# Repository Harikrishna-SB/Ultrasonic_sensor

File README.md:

# Ultrasonic_sensor

Interfacing ultrasonic sensor without a micro-controller

HCSR04 has 4 pins..the usual vcc,gnd and trig(stands for trigger) and echo
for more details:

This project aims to read the sensor data convert it to proper units and display on a seven segment display..

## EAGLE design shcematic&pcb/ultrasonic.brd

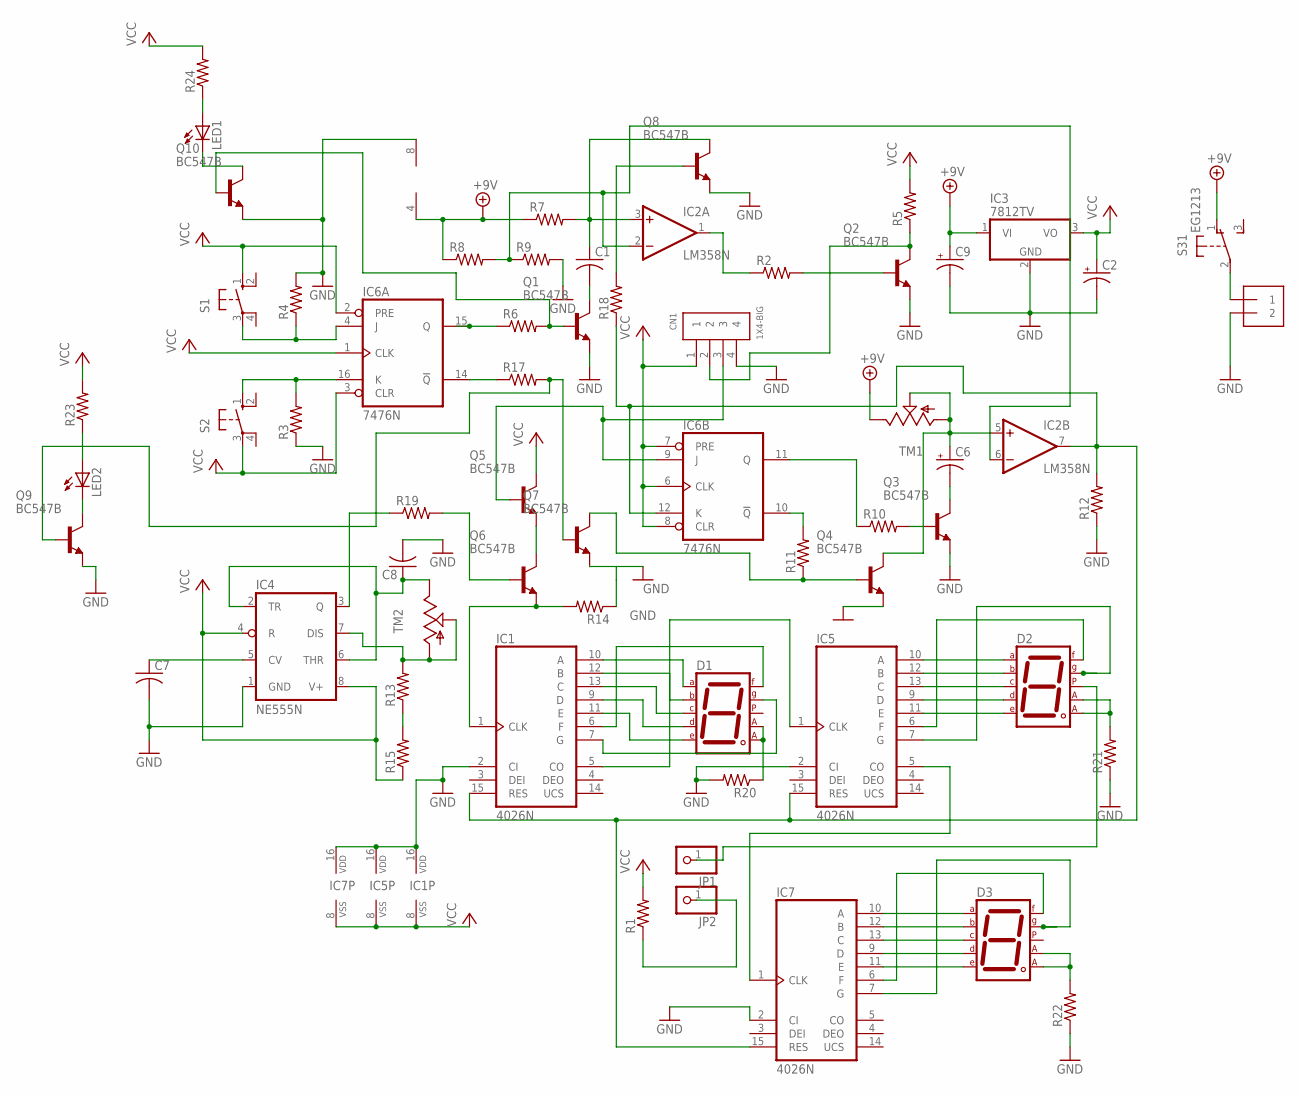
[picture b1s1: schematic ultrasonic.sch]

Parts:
C1, C7, C8: C-US025-040X050; C025-040X050
C2: CPOL-USE2-4; E2-4
C6, C9: CPOL-USE2.5-6; E2,5-6
CN1: 1X4-BIG; 1X04-BIG
D1, D2, D3: 7SEG-CA; 7SEG-13
IC1, IC5, IC7: 4026N; DIL16
IC2: LM358N; DIL08
IC3: 7812TV; TO220V
IC4: NE555N; DIL08-ROUND
IC6: 7476N; DIL16
J1: 1X2-3.5MM
JP1, JP2: PINHD-1X1; 1X01
LED1, LED2: LED5MM
Q1, Q2, Q3, Q4, Q5, Q6, Q7, Q8, Q9, Q10: BC547B; TO92
R1, R2, R3, R4, R5, R6, R7, R8, R9, R10, R11, R12, R13, R14, R15, R17, R18, R19, R20, R21, R22, R23, R24: R-US_0204/7; 0204/7
S1, S2: 10-XX; B3F-10XX
S3: EG1213
TM1, TM2: TRIM; 6MM

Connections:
+9V: C9.+, IC2.4 (V-), IC3.1 (VI), R7.1, R8.1, S3.1 (O), TM1.E
GND: C2.-, C7.2, C8.2, C9.-, CN1.4, IC1.2 (CI), IC1.16 (VDD), IC2.8 (V+), IC3.2 (GND), IC4.1 (GND), IC5.2 (CI), IC5.16 (VDD), IC6.13 (GND), IC7.2 (CI), IC7.16 (VDD), J1.2, Q1.1 (E), Q2.1 (E), Q3.1 (E), Q4.1 (E), Q7.1 (E), Q8.1 (E), Q9.1 (E), Q10.1 (E), R3.1, R4.2, R9.2, R12.1, R14.1, R20.2, R21.1, R22.1
unnamed: IC2.1 (OUT), R2.1
unnamed: C1.2, Q1.3 (C)
unnamed: IC6.16 (K), R3.2, S2.1 (S)
unnamed: IC6.4 (J), R4.1, S1.3
unnamed: IC4.3 (Q), R19.1
unnamed: C1.1, IC2.3 (+IN), Q8.3 (C), R7.2
unnamed: Q1.2 (B), Q10.2 (B), R6.2
unnamed: IC6.14 (!Q), R17.1
unnamed: CN1.2, Q2.3 (C), R5.1
unnamed: IC2.2 (-IN), IC2.6 (-IN), R8.2, R9.1
unnamed: Q2.2 (B), R2.2
unnamed: Q6.2 (B), R19.2
unnamed: IC1.15 (RES), IC2.7 (OUT), IC5.15 (RES), IC6.12 (K), IC7.15 (RES), R12.2, R18.1
unnamed: C7.1, IC4.5 (CV)
unnamed: CN1.3, IC6.9 (J), Q5.2 (B)
unnamed: C6.+, IC2.5 (+IN), Q4.3 (C), TM1.A, TM1.S
unnamed: C6.-, Q3.3 (C)
unnamed: IC6.11 (Q), R10.1
unnamed: Q3.2 (B), R10.2
unnamed: IC6.10 (!Q), R11.2
unnamed: Q4.2 (B), Q7.3 (C), R11.1
unnamed: D1.7 (A), IC1.10 (A)
unnamed: D1.3 (CA1), D1.8 (CA2), R20.1
unnamed: Q5.1 (E), Q6.3 (C)
unnamed: JP2.1, R1.1
unnamed: D1.6 (B), IC1.12 (B)
unnamed: C8.1, IC4.2 (TR), IC4.6 (THR), TM2.E
unnamed: D1.2 (D), IC1.9 (D)
unnamed: D1.4 (C), IC1.13 (C)
unnamed: IC1.1 (CLK), Q6.1 (E), R14.2
unnamed: D1.1 (E), IC1.11 (E)
unnamed: D1.9 (F), IC1.6 (F)
unnamed: D1.10 (G), IC1.7 (G)
unnamed: IC1.5 (CO), IC5.1 (CLK)
unnamed: D2.3 (CA1), D2.8 (CA2), R21.2
unnamed: D2.7 (A), IC5.10 (A)
unnamed: D2.6 (B), IC5.12 (B)
unnamed: D2.4 (C), IC5.13 (C)
unnamed: D2.2 (D), IC5.9 (D)
unnamed: D2.1 (E), IC5.11 (E)
unnamed: D2.9 (F), IC5.6 (F)
unnamed: R13.1, R15.2
unnamed: IC4.7 (DIS), R13.2, TM2.A, TM2.S
unnamed: D2.10 (G), IC5.7 (G)
unnamed: Q7.2 (B), Q9.2 (B), R17.2
unnamed: IC6.15 (Q), R6.1
unnamed: IC5.5 (CO), IC7.1 (CLK)
unnamed: Q8.2 (B), R18.2
unnamed: J1.1, S3.2
unnamed: D2.5 (DP), JP1.1
unnamed: D3.7 (A), IC7.10 (A)
unnamed: D3.6 (B), IC7.12 (B)
unnamed: D3.4 (C), IC7.13 (C)
unnamed: D3.2 (D), IC7.9 (D)
unnamed: D3.1 (E), IC7.11 (E)
unnamed: D3.9 (F), IC7.6 (F)
unnamed: D3.10 (G), IC7.7 (G)
unnamed: D3.3 (CA1), D3.8 (CA2), R22.2
unnamed: LED2.A, R23.1
unnamed: LED2.K (C), Q9.3 (C)
unnamed: LED1.K (C), Q10.3 (C)
unnamed: LED1.A, R24.1
VCC: C2.+, CN1.1, IC1.8 (VSS), IC3.3 (VO), IC4.4 (R), IC4.8 (V+), IC5.8 (VSS), IC6.1 (CLK), IC6.2 (PRE), IC6.3 (CLR), IC6.5 (VCC), IC6.6 (CLK), IC6.7 (PRE), IC6.8 (CLR), IC7.8 (VSS), Q5.3 (C), R1.2, R5.2, R15.1, R23.2, R24.2, S1.1 (S), S2.3

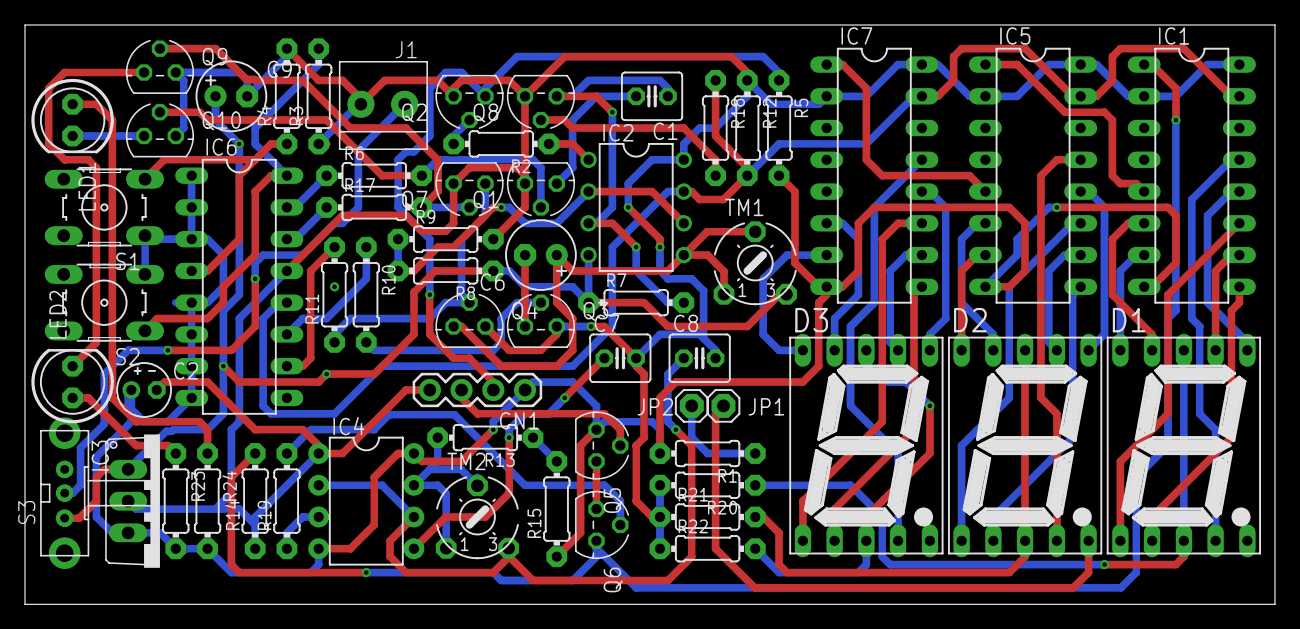
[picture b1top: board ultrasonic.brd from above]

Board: 2 copper layers, 100.0 x 46.3 mm, 60 parts (0 on the bottom side), 65 nets.

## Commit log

2020-04-02 A bit
2020-04-02 schematic and layout added
